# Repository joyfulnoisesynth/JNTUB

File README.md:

# JoyfulNoise Tiny Utility Board

A versatile ATtiny85-powered Eurorack module in 4HP.

## License

JoyfulNoise hardware and software is Open Source.

The JNTUB hardware is licensed under Creative Commons: [CC-BY-SA-4.0: Attribution / ShareAlike](https://creativecommons.org/licenses/by-sa/4.0/).

The JNTUB firmware is licensed under the GNU General Public License: [GPLv3](https://www.gnu.org/licenses/gpl-3.0-standalone.html).

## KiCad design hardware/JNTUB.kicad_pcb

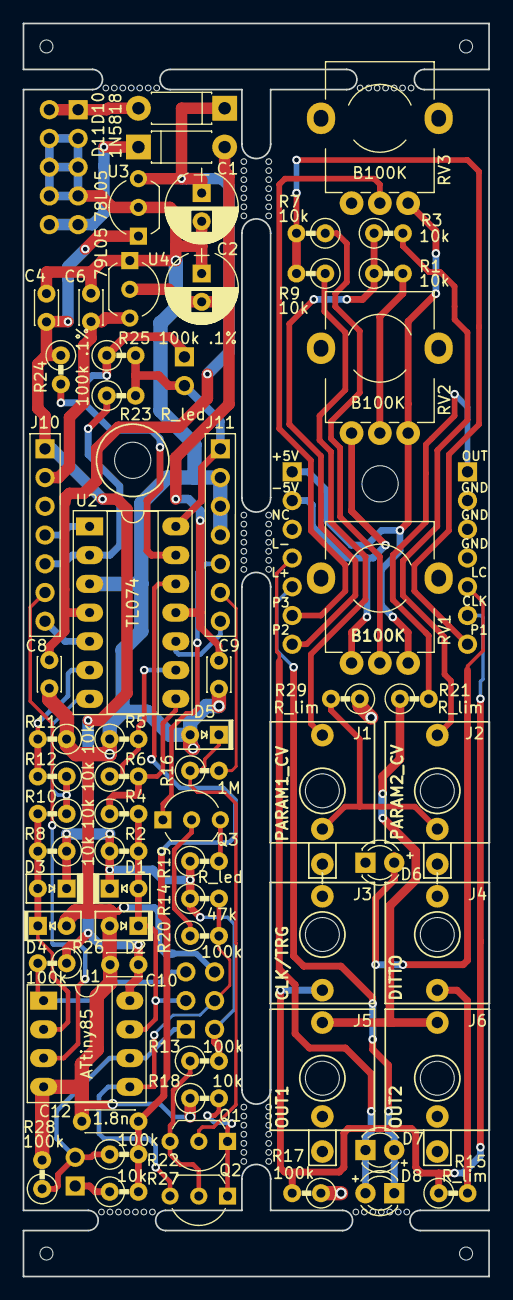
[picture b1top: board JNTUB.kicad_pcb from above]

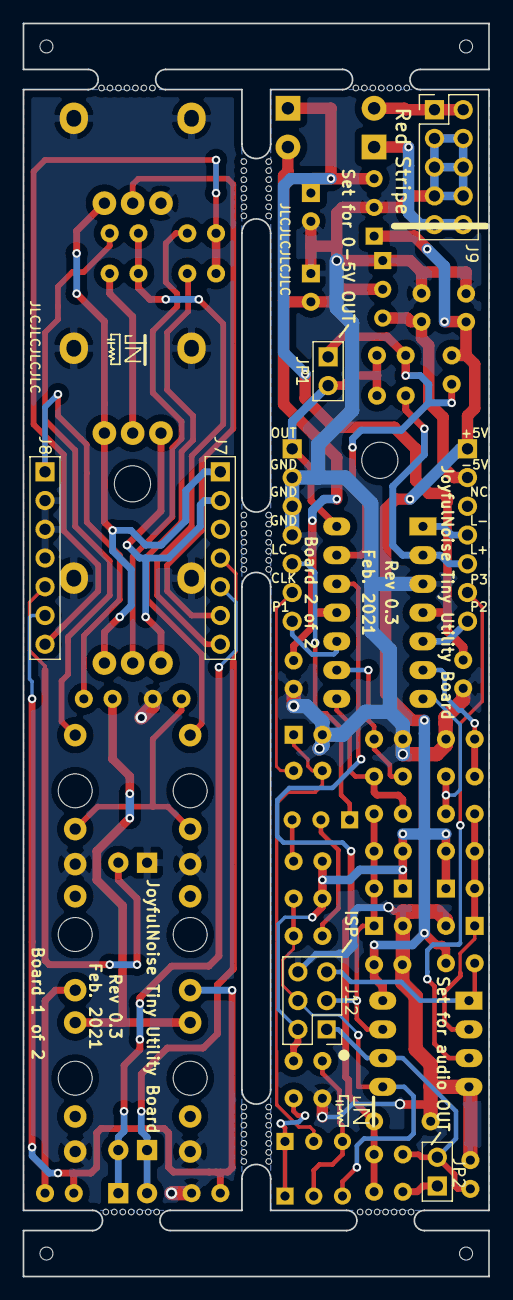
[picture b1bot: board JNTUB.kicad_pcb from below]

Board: 2 copper layers, 41.1 x 110.7 mm, 80 parts (6 on the bottom side), 47 nets.

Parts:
C1, C2: 22u; CP_Radial_D6.3mm_P2.50mm
C4, C6, C8, C9, C10: 0.1u; C_Disc_D3.0mm_W2.0mm_P2.50mm
C12: 1.8n; C_Disc_D4.3mm_W1.9mm_P5.00mm
D1, D3: BAT81; D_DO-35_SOD27_P2.54mm_Vertical_AnodeUp
D2, D4: BAT81; D_DO-35_SOD27_P2.54mm_Vertical_KathodeUp
D5: 1N4148; D_DO-35_SOD27_P2.54mm_Vertical_KathodeUp
D6, D7, D8: LED; LED_D3.0mm
D10, D11: 1N5818; D_DO-41_SOD81_P7.62mm_Horizontal
H1, H2: MountingHole; MountingHole_3.2mm_M3
J1: PARAM1_CV; PJ301M-12_Thonkiconn
J2: PARAM2_CV; PJ301M-12_Thonkiconn
J3: CLK/TRG; PJ301M-12_Thonkiconn_NoGround
J4: DITTO; PJ301M-12_Thonkiconn_NoGround
J5: OUT1; PJ301M-12_Thonkiconn
J6: OUT2; PJ301M-12_Thonkiconn
J7: B1_HDR_LEFT; Pin_Header_Straight_1x07_Pitch2.54mm
J8: B1_HDR_RIGHT; Pin_Header_Straight_1x07_Pitch2.54mm
J9: POWER; Pin_Header_Straight_2x05_Pitch2.54mm
J10: B2_HDR_LEFT; Pin_Header_Straight_1x07_Pitch2.54mm
J11: B2_HDR_RIGHT; Pin_Header_Straight_1x07_Pitch2.54mm
J12: ISP; Pin_Header_Straight_2x03_Pitch2.54mm
JP1: JMP_UNIPOLAR; Pin_Header_Straight_1x02_Pitch2.54mm
JP2: JMP_AUDIO; Pin_Header_Straight_1x02_Pitch2.54mm
Q1, Q2, Q3: 2N3904; TO-92_Inline_Wide
R1, R2, R3, R4, R5, R6, R7, R8, R9, R10, R11, R12, R18, R27: 10k; R_Axial_DIN0207_L6.3mm_D2.5mm_P2.54mm_Vertical
R13, R17, R20, R22, R26, R28: 100k; R_Axial_DIN0207_L6.3mm_D2.5mm_P2.54mm_Vertical
R14: 47k; R_Axial_DIN0207_L6.3mm_D2.5mm_P2.54mm_Vertical
R15, R21, R29: R_lim; R_Axial_DIN0207_L6.3mm_D2.5mm_P2.54mm_Vertical
R16: 1M; R_Axial_DIN0207_L6.3mm_D2.5mm_P2.54mm_Vertical
R19, R23: R_led; R_Axial_DIN0207_L6.3mm_D2.5mm_P2.54mm_Vertical
R24, R25: 100k .1%; R_Axial_DIN0207_L6.3mm_D2.5mm_P2.54mm_Vertical
RV1, RV2, RV3: B100K; Potentiometer_Alpha_9mm_WithGround
U1: ATtiny85; DIP-8_W7.62mm_Socket_LongPads
U2: TL074; DIP-14_W7.62mm_Socket_LongPads
U3: 78L05; TO-92_Inline_Wide
U4: 79L05; TO-92_Inline_Wide
mouse-bite-2.54mm-slot, mouse-bite-2.54mm-slot#2, mouse-bite-2.54mm-slot#3: VAL**; mouse-bite-2.54mm-slot-long
mouse-bite-2mm-slot, mouse-bite-2mm-slot#2, mouse-bite-2mm-slot#3, mouse-bite-2mm-slot#4: VAL**; mouse-bite-2mm-slot-long-single

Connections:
+5V: C4.1, C10.1, D1.1, D3.1, J7.1, J10.1, J12.2, R2.1, R8.1, R13.2, R14.1, R19.1, R24.1, R26.1, RV1.3, RV2.3, RV3.3, U1.8, U3.1
+12V: C1.1, C8.1, D10.1, U2.4, U3.3
-5V: C6.2, J7.2, J10.2, RV1.1, RV2.1, U4.3
-12V: C2.2, C9.2, D11.2, U2.11, U4.2
/MainBoard/CLK_LED: J11.5, Q3.1
/MainBoard/CLK_TRG: J11.6, R16.2
/MainBoard/LED_NEG: J10.4, U2.1
/MainBoard/LED_POS: J10.5, R23.1, U2.2
/MainBoard/MCU_ADC1: D1.2, D2.1, J12.3, R2.2, R4.2, U1.7
/MainBoard/MCU_ADC2: J10.6, U1.3
/MainBoard/MCU_ADC3: D3.2, D4.1, R8.2, R10.2, U1.2
/MainBoard/MCU_PB0: J12.4, Q2.3, R14.2, R20.2, U1.5
/MainBoard/MCU_PWM: J12.1, JP2.2, R22.1, R28.1, U1.6
/MainBoard/MCU_RESET: J12.5, R26.2, U1.1
/MainBoard/OUT: J11.1, JP1.2, R23.2, R25.2, U2.14
/MainBoard/P1_AVG: J11.7, U2.10
/MainBoard/P2_AVG: J10.7, U2.5
/PeripheralBoard/CLK_LED: D6.2, J8.5
/PeripheralBoard/CLK_TRG: J3.3, J8.6, R15.1, R17.2
/PeripheralBoard/DITTO: J4.3, R15.2
/PeripheralBoard/LED_NEG: D7.1, D8.2, J7.4
/PeripheralBoard/LED_POS: D7.2, D8.1, J7.5
/PeripheralBoard/OUT: J8.1, R21.2
/PeripheralBoard/OUT1: J5.3, J6.3, R21.1
/PeripheralBoard/P1_AVG: J8.7, R7.2, R9.2
/PeripheralBoard/P1_CV: J1.3, R9.1
/PeripheralBoard/P1_POT: R7.1, RV1.2
/PeripheralBoard/P2_AVG: J7.7, R1.1, R3.1
/PeripheralBoard/P2_CV: J2.3, R3.2
/PeripheralBoard/P2_POT: R1.2, RV2.2
/PeripheralBoard/P3_POT: J7.6, RV3.2
GNDREF: C1.2, C2.1, C4.2, C6.1, C8.2, C9.1, C10.2, C12.2, D2.2, D4.2, D5.2, D6.1, J1.1, J2.1, J5.1, J6.1, J8.2, J8.3, J8.4, J9.3, J9.4, J9.5, J9.6, J9.7, J9.8, J11.2, J11.3, J11.4, J12.6, R5.1, R11.1, R17.1, R18.1, R28.2, R29.1, RV1.MP, RV2.MP, RV3.1, RV3.MP, U1.4, U2.3, U3.2, U4.1
unnamed: C12.1, R22.2, R27.2, U2.12
unnamed: D5.1, Q1.2, R16.1
unnamed: D10.2, J9.1, J9.2
unnamed: D11.1, J9.9, J9.10
unnamed: J1.2, J2.2, R29.2
unnamed: JP1.1, R24.2, R25.1, U2.13
unnamed: JP2.1, R27.1
unnamed: Q1.1, Q2.1, R18.2
unnamed: Q1.3, Q2.2, R13.1
unnamed: Q3.2, R20.1
unnamed: Q3.3, R19.2
unnamed: R4.1, R6.2, U2.8
unnamed: R5.2, R6.1, U2.9
unnamed: R10.1, R12.1, U2.7
unnamed: R11.2, R12.2, U2.6

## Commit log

2020-12-29 Add Libraries submodule
2020-12-29 Use project-local libraries for portability
2020-12-29 Move Libraries to hardware folder (oops)
2020-12-29 Remove suffix from submodule url
    I have to set my remotes to github.com-joyfulnoisesynth so I can
    work with the SSH key for that account, but if I leave that suffix
    in the submodule url, GitHub doesn't realize the submodule comes
    from another GitHub repo.
    Luckily, it seems like the main repo's configuration passes through
    to the submodules, so I don't even need the suffix there!
2020-12-30 [JNTUB-fw] Create JNTUB library
2020-12-30 [JNTUB-fw] Add test pin mappings for ATmega328p
2020-12-30 [JNTUB-fw] Add Test sketch to test JNTUB library
    Also, I was wrong about gate being inverted, fix that.
2021-01-01 [JNTUB-HW] Overhaul PCB layout
    - Make traces and clearances much bigger than first attempt
    - Remove test points and resistor leading to MCU RESET
    - Move some resistors to peripheral board
    - Space out remaining components on main board
2021-01-01 [JNTUB-HW] Clean up PCB v0.1 for fabrication
2021-01-01 [JNTUB-HW] Write script to copy PCB for splitting
    Need to have separate Gerber files for each board.
2021-01-01 [JNTUB-HW] Swap front and back copper layers
2021-01-01 [JNTUB-HW] Clean up straggling traces
2021-01-01 [JNTUB-HW] Add JLCPCB note for part number
2021-01-01 [JNTUB-HW] Generate Gerber files for PCB v0.1
2021-01-01 [JNTUB-HW] Update schematic PDF for v0.1
2021-01-01 [JNTUB-fw] Update JNTUB lib interface
    Also lay groundwork for fast PWM
2021-01-01 [JNTUB-fw] Add copyrightpasta to Test sketch
2021-01-01 [JNTUB-fw] Create DiscreteKnob class
2021-01-01 [JNTUB-fw] Add keywords.txt to JNTUB Arduino lib
2021-01-01 [BeatTool] Create BeatTool firmware skeleton
2021-01-01 [JNTUB-fw] Move copyrightpastas to very top
2021-01-01 [D-RAND] Create D-RAND firmware skeleton
2021-01-02 [JNTUB-fw] Add JNTUB::Clock class
2021-01-02 [JNTUB-fw] Modify interface for JNTUB modules
2021-01-02 [BeatTool] Refactor to follow new interface
2021-01-03 [JNTUB-fw] Rewrite DiscreteKnob and add CurveKnob
2021-01-03 [JNTUB-fw] Fix up Clock and CurveKnob
2021-01-03 [JNTUB-fw] Give CurveKnob more hysteresis
2021-01-03 [BeatTool] Initial attempt at implementation
2021-01-03 [JNTUB-fw] Make DiscreteKnob max val 256 (not 255)
2021-01-03 [JNTUB-fw] Add valueChanged() to DiscreteKnob
2021-01-03 [JNTUB-fw] Add Stopwatch to handle timer overflow
2021-01-03 [JNTUB-fw] Add EdgeDetector class
2021-01-04 [JNTUB-fw] Fix compile errors
2021-01-04 [BeatTool] Implement Mult/Div mode
2021-01-04 [JNTUB-fw] Implement fast PWM setup
2021-01-04 [JNTUB-fw] Copyright 2020 --> 2021
2021-01-04 [BeatTool] Fix bugs in multiply mode
2021-01-06 [D-RAND] Initial implementation
2021-01-06 [JNTUB-HW] Move front panel to separate PCB file
2021-01-08 [JNTUB-HW] Finish v0.1 of front panel
2021-01-08 [JNTUB-fw] Get rid of the dumb abstractions
    Also clean things up a bit
2021-01-08 [JNTUB-fw] Make Clock syncable while stopped
2021-01-08 [BeatTool] Improve Clock and Burst modes
    * Give better rate ranges for both Clock and Burst modes.
    * Run both modes off milliseconds rather than microseconds.
2021-01-08 [BeatTool] Exact clock division for whole divisors
2021-01-08 [D-RAND] Change param3 from Bias to Slew
2021-01-18 [JNTUB-HW] JNTUB Hardware Revision 0.2
    * Add resistor to drain C12 (PWM filter cap)
    * Add optional parallel resistor to PWM filter
    * selectable by jumper
    * increases the cutoff frequency to audio range
    * Add resistor between 5V and MCU RESET to allow for ISP
    * Move a few resistors to Board 1
2021-01-18 [JNTUB-HW] Generate Gerber files for v0.2
2021-01-18 [BeatTool] Change mult/div at onset of period
2021-01-20 [JNTUB-HW] Re-export panel as old gerber (for JLC)
2021-01-20 [JNTUB-fw] Add audio setup function to library
2021-01-20 [Karplus] Initial implementation
2021-01-23 [D-VCO] Initial implementation
2021-01-31 [Karplus] Fix things and experiment a bit
    * Fix weighted average arithmetic bug
    * Fix blend parameter
    * Try new weights for weighted average
2021-01-31 [JNTUB-fw] Version-specific pin mappings
    The pin mappings changed between hardware v0.1 and v0.2.
    Since I have test units with both hardware versions, I
    added the ability to #define HW_VER_0_1 before importing
    JNTUB.h to change them.
2021-01-31 [ENV] Initial implementation
2021-02-05 [JNTUB-HW] Shift panel holes down a bit
2021-02-05 [JNTUB-HW] Modify resistor values in schematic
2021-02-05 [JNTUB-HW] Some PCB and schematic updates
    * Thicker silkscreen on diodes
    * Give explicit values to some items
    * Update potentiometer schematic symbols
    * Fix some symbol names
2021-02-06 [JNTUB-HW] Create SMD version of PCB
    Use KiCad scripting API to write a script to turn most
    through-hole parts into SMT parts. Will use this to release
    two variants of the board.
    Had to reroute many traces so that every through hole pad is
    connected to traces on the front layer (that way, when all
    the through holes are removed, the components are still
2021-02-07 [JNTUB-HW] PCB now preparable for SMT assembly!
2021-02-07 [JNTUB-HW] Import Simon's panel designs into KiCad
2021-02-08 [JNTUB-fw] Implement a 10-bit PWM procedure
2021-02-08 [JNTUB-HW] Prepare a smaller mfg batch of panels
2021-02-08 [JNTUB-HW] smd_convert script works on file
2021-02-09 [JNTUB-HW] JNTUB Hardware Revision 0.3
2021-02-09 [JNTUB-HW] Generate Gerber files for v0.3
2021-02-09 [JNTUB-fw] Rename AudioInterrupt -> TimerInterrupt
    Gonna also use this facility for FastClock in the next commit
2021-02-10 [JNTUB-fw] Create FastClock class
2021-02-10 [ENV] Reimplement with FastClock
2021-02-10 [LFO] Initial implementation
2021-02-12 [JNTUB-fw] Better timer interrupt support
2021-02-12 [JNTUB-fw] Make 10-bit PWM actually work
2021-02-12 [LFO] Use 10-bit PWM for less chunky output
2021-02-12 [ENV] Use interpolation for smoother envelopes
2021-02-12 [LFO] Fix bug where amplitude was 1/4 of expected
2021-02-14 [JNTUB-fw] Construct FastClock with a sample rate
2021-03-18 [JNTUB-fw] Pin mappings for HW v0.3
2021-03-22 [JNTUB-fw] Create To-Do list for JNTUB firmware
2021-03-22 [JNTUB-fw] Refactor `FastClock` a bit
2021-03-22 [JNTUB-fw] Implement automatic clock detection
2021-03-22 [JNTUB-fw] Edit the To-Do a bit
2021-03-22 [LFO] Fix the WT_SQUARE wavetable
2021-03-22 [LFO] Implement clocked mode using `ClockDetector`
